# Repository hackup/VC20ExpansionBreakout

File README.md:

# Commodore VC20/VIC20 Cartridge Port Breakout

This is an adapter board for the [cartridge port](https://en.wikipedia.org/wiki/Commodore_VIC-20#Ports_and_sockets) of the Commodore VIC20 aka. VC20. It connects the cartridge port to a standard 830 pin prototyping breadboard to assist with the development of modules or cartridges.

Additionally, it features an optional on-board slot for either a 27c512 or 27c020 EPROM. The data bus lines D0-D7 and the address bus lines A0-A12 are connected directly to the slot, as are GND and the 5V power rail. The remaining address bus lines of the EPROM and CE/OE are available on J4. Jumper JP1 must be closed if a 27c512 chip is used.

**USE AT YOUR OWN RISK!**

This adapter was modelled after my similar [breakout-board for the C64](https://github.com/hackup/C64ExpansionBreakout).

## License
[
](http://creativecommons.org/licenses/by-nc-sa/4.0/)

This work is licensed under a
[Creative Commons Attribution-NonCommercial-ShareAlike 4.0 International License](http://creativecommons.org/licenses/by-nc-sa/4.0/).

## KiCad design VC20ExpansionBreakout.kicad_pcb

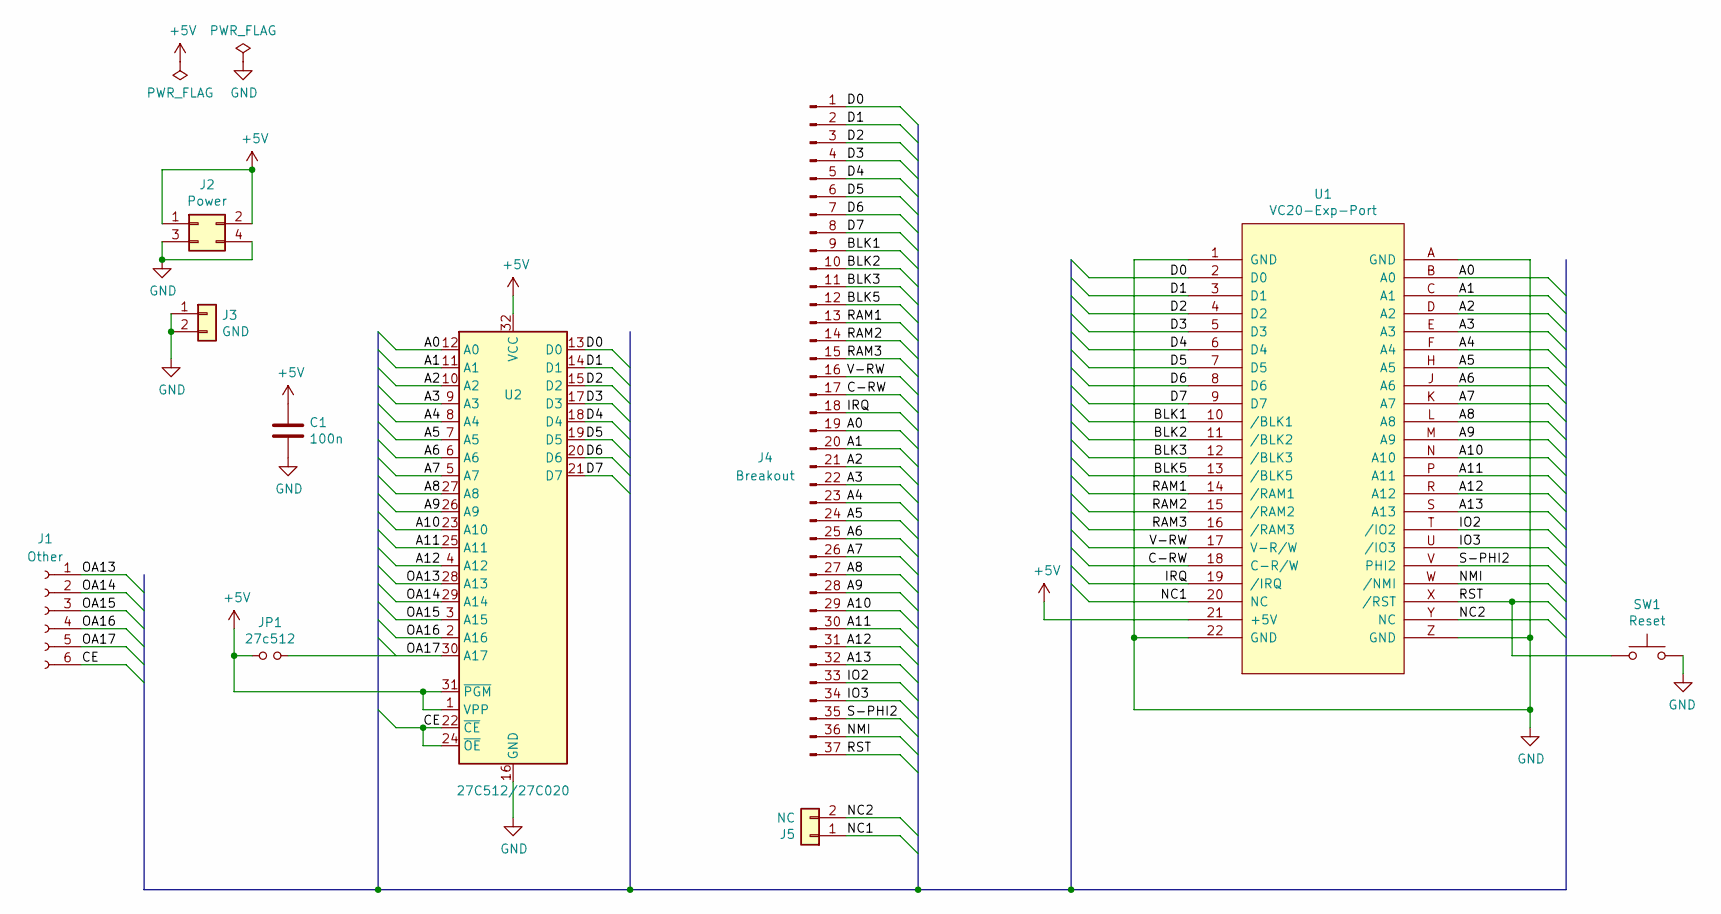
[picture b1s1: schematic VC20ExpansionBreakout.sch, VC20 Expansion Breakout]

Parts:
C1: 100n; C_Disc_D4.3mm_W1.9mm_P5.00mm
J1: Other; PinSocket_1x06_P2.54mm_Vertical
J2: Power; PinHeader_2x02_P2.54mm_Vertical
J3: GND; PinHeader_1x02_P2.54mm_Vertical
J4: Breakout; PinHeader_1x37_P2.54mm_Vertical
J5: NC; PinSocket_1x02_P2.54mm_Vertical
JP1: 27c512; PinHeader_1x02_P2.54mm_Vertical
SW1: Reset; SW_PUSH_6mm
U1: VC20-Exp-Port; VC20-Cart
U2: 27C512/27C020; DIP-32_W15.24mm_Socket_LongPads

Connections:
+5V: C1.1, J2.1, J2.2, JP1.1, U1.21 (+5V), U2.1 (VPP), U2.31 (~PGM), U2.32 (VCC)
/A0: J4.19, U1.B (A0), U2.12 (A0)
/A1: J4.20, U1.C (A1), U2.11 (A1)
/A2: J4.21, U1.D (A2), U2.10 (A2)
/A3: J4.22, U1.E (A3), U2.9 (A3)
/A4: J4.23, U1.F (A4), U2.8 (A4)
/A5: J4.24, U1.H (A5), U2.7 (A5)
/A6: J4.25, U1.J (A6), U2.6 (A6)
/A7: J4.26, U1.K (A7), U2.5 (A7)
/A8: J4.27, U1.L (A8), U2.27 (A8)
/A9: J4.28, U1.M (A9), U2.26 (A9)
/A10: J4.29, U1.N (A10), U2.23 (A10)
/A11: J4.30, U1.P (A11), U2.25 (A11)
/A12: J4.31, U1.R (A12), U2.4 (A12)
/A13: J4.32, U1.S (A13)
/BLK1: J4.9, U1.10 (/BLK1)
/BLK2: J4.10, U1.11 (/BLK2)
/BLK3: J4.11, U1.12 (/BLK3)
/BLK5: J4.12, U1.13 (/BLK5)
/C-RW: J4.17, U1.18 (C-R/W)
/CE: J1.6, U2.22 (~CE), U2.24 (~OE)
/D0: J4.1, U1.2 (D0), U2.13 (D0)
/D1: J4.2, U1.3 (D1), U2.14 (D1)
/D2: J4.3, U1.4 (D2), U2.15 (D2)
/D3: J4.4, U1.5 (D3), U2.17 (D3)
/D4: J4.5, U1.6 (D4), U2.18 (D4)
/D5: J4.6, U1.7 (D5), U2.19 (D5)
/D6: J4.7, U1.8 (D6), U2.20 (D6)
/D7: J4.8, U1.9 (D7), U2.21 (D7)
/IO2: J4.33, U1.T (/IO2)
/IO3: J4.34, U1.U (/IO3)
/IRQ: J4.18, U1.19 (/IRQ)
/NC1: J5.1, U1.20 (NC)
/NC2: J5.2, U1.Y (NC)
/NMI: J4.36, U1.W (/NMI)
/OA13: J1.1, U2.28 (A13)
/OA14: J1.2, U2.29 (A14)
/OA15: J1.3, U2.3 (A15)
/OA16: J1.4, U2.2 (A16)
/OA17: J1.5, JP1.2, U2.30 (A17)
/RAM1: J4.13, U1.14 (/RAM1)
/RAM2: J4.14, U1.15 (/RAM2)
/RAM3: J4.15, U1.16 (/RAM3)
/RST: J4.37, SW1.2, U1.X (/RST)
/S-PHI2: J4.35, U1.V (PHI2)
/V-RW: J4.16, U1.17 (V-R/W)
GND: C1.2, J2.3, J2.4, J3.1, J3.2, SW1.1, U1.1 (GND), U1.22 (GND), U1.A (GND), U1.Z (GND), U2.16 (GND)

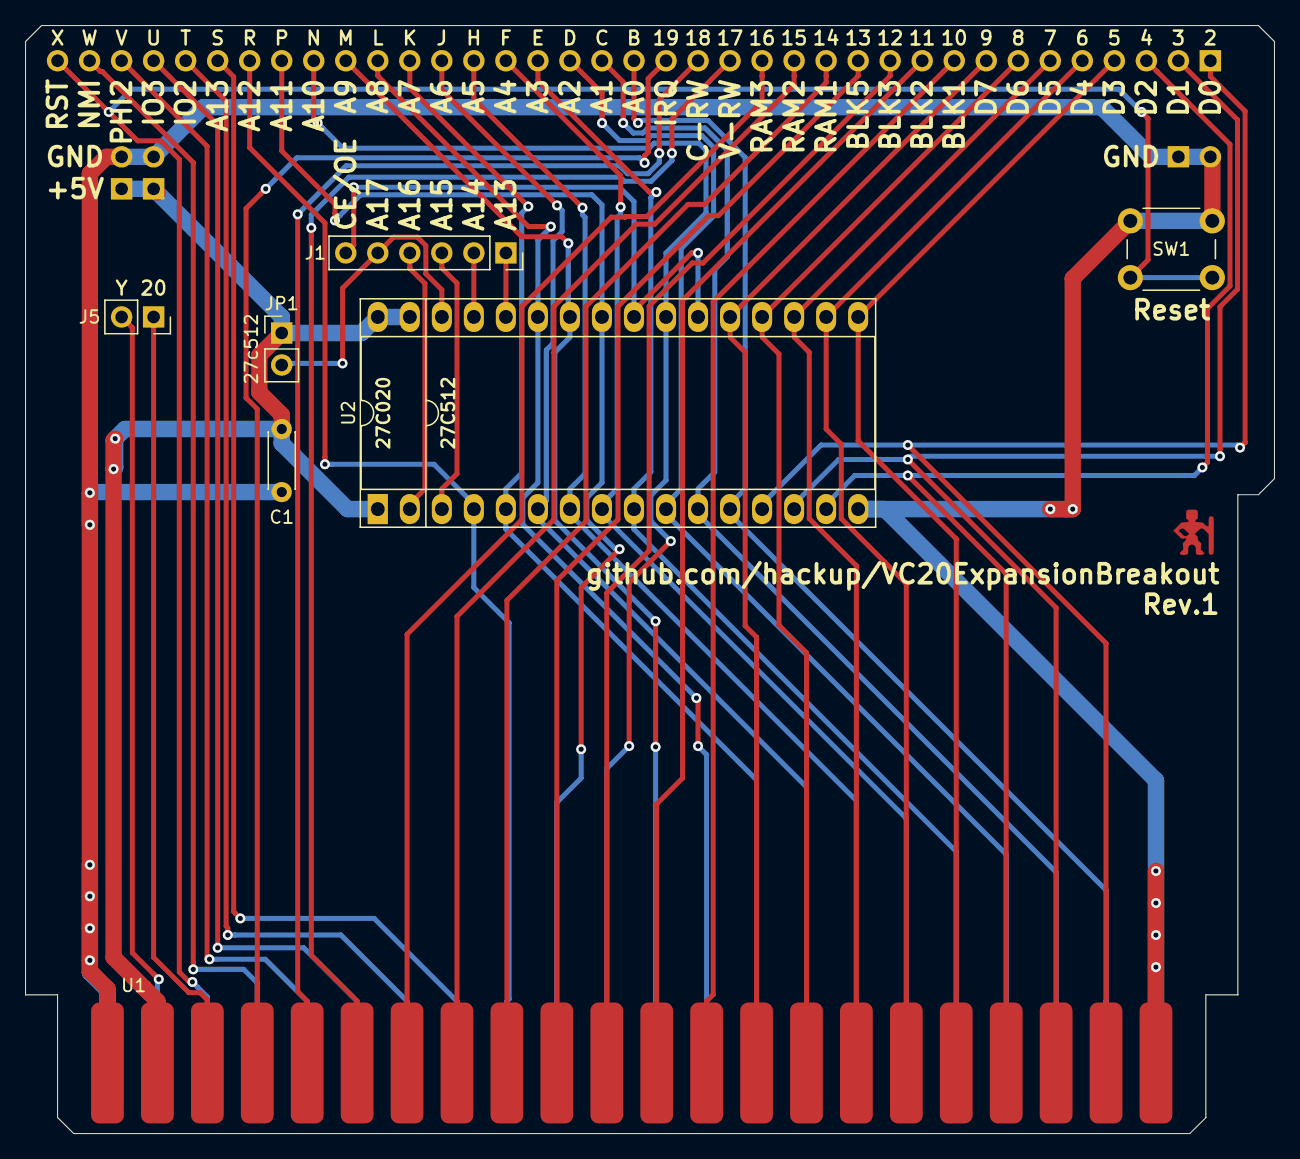
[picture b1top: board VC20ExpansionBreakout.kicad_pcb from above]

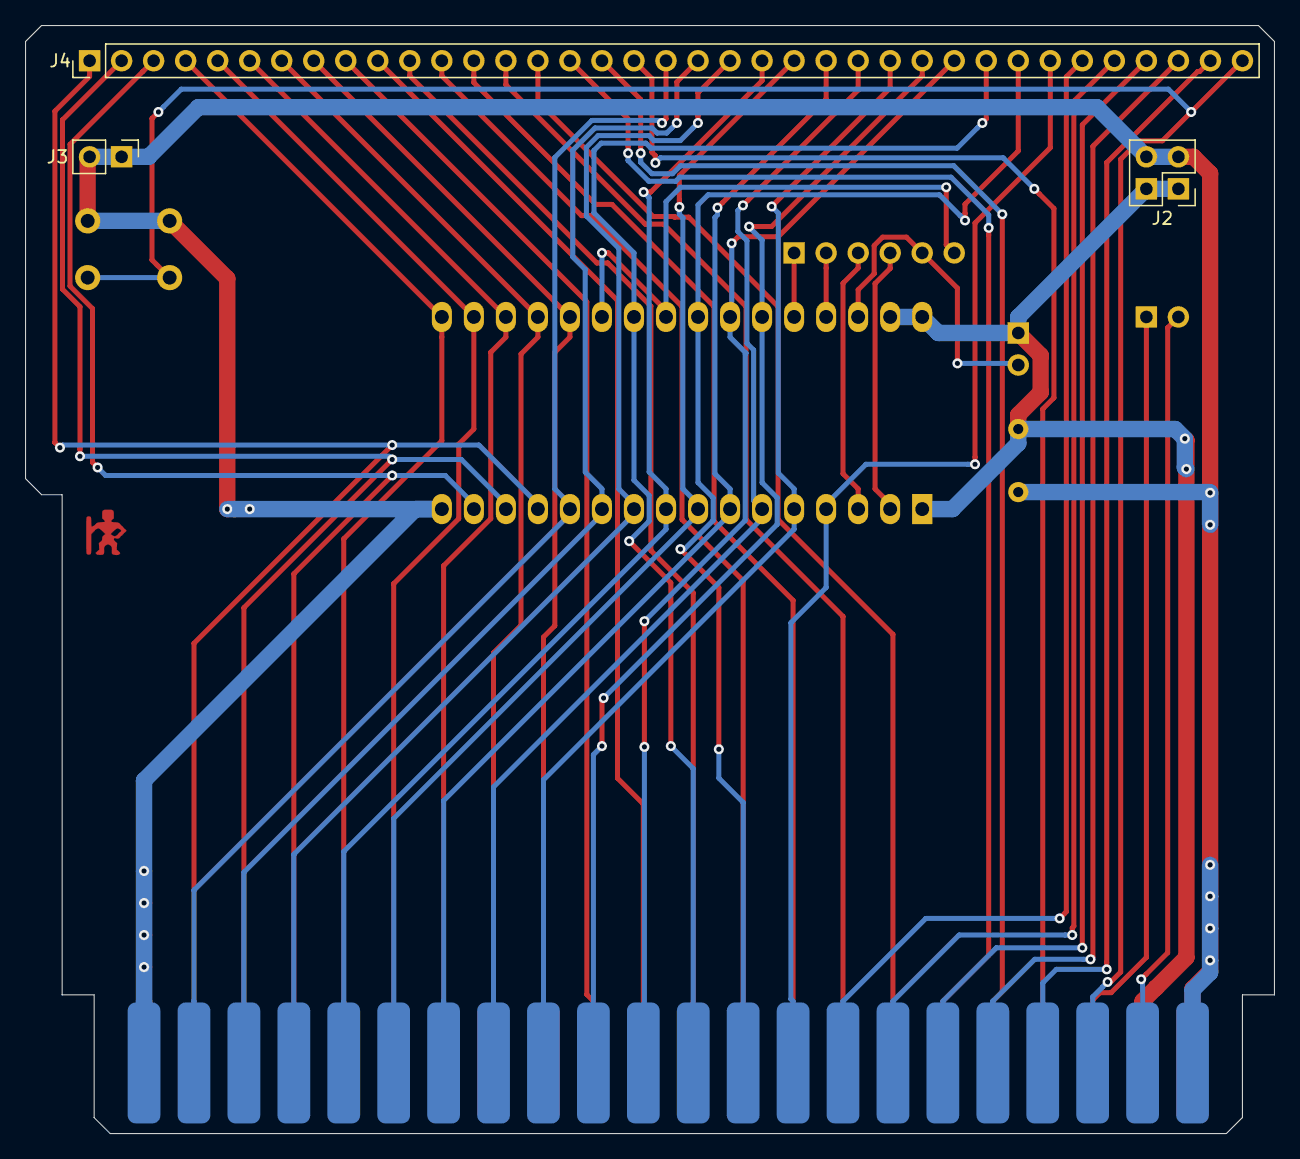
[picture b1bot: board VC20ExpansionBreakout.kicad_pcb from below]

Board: 2 copper layers, 99.1 x 87.9 mm, 10 parts (3 on the bottom side), 47 nets.

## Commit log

2020-01-22 Initial commit.
2020-01-22 Added missing connections.
2020-01-22 Fixing silk-screen.
2020-01-23 Fine tuning.
2020-01-23 Dimensions.
2020-01-24 Prepare gerber export.
2020-03-29 Added README.
